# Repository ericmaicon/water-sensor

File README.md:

# About it

This is a project for a master degree with the goal of store water flow data in a house.

It uses a flow sensor, connected on an ESP8266 to send it thought the internet to an endpoint.
It has a USBSerial to update the ESP8266 firmware and code.

* [Roadmap](https://github.com/ericmaicon/water-sensor/blob/master/docs/Roadmap.md)

Some research about ESP8266:

* [Espruino firmware](https://github.com/ericmaicon/water-sensor/blob/master/docs/Espruino.md)
* [NodeLUA firmware](https://github.com/ericmaicon/water-sensor/blob/master/docs/Nodelua.md)
* [NodeMCU firmware](https://github.com/ericmaicon/water-sensor/blob/master/docs/Nodemcu.md)
* [AT firmware](https://github.com/ericmaicon/water-sensor/blob/master/docs/AT.md)

Raspberry:

* [Install Debian on Raspberry from Mac](https://github.com/ericmaicon/water-sensor/blob/master/docs/Install-Raspberry.md)
* [Using raspberry and ESP8266 as router](https://github.com/ericmaicon/water-sensor/blob/master/docs/Raspberry.md)

# Useful Links

## Schematics
* [Convert 5V to 3.3V](http://kb.kaminskiengineering.com/node/171)
* [Convert AC to DC](http://www.elprocus.com/steps-to-convert-the-230v-ac-to-5v-dc/)

## Flow Sensor
* [Sensor](http://www.seeedstudio.com/wiki/G1'1/4_Water_Flow_sensor)
* [Datasheet](http://www.seeedstudio.com/depot/datasheet/water%20flow%20sensor%20datasheet.pdf)
* [Datasheet](http://www.hobbytronics.co.uk/datasheets/sensors/YF-S201.pdf)
* [Portuguese Tutorial](http://labdegaragem.com/profiles/blogs/tutorial-como-utilizar-o-sensor-de-fluxo-de-agua)
* [Code example](http://www.hobbytronics.co.uk/download/YF-S201.ino)
* [Tutorial](http://diyhacking.com/arduino-flow-rate-sensor/)
* [Code example](http://diyhacking.com/projects/FlowMeterDIY.ino)

## ESP8266
* [GPIO API](http://esp8266.co.uk/tutorials/introduction-to-the-gpio-api/)
* [Flow Sensor and ESP8266](http://www.esp8266.com/viewtopic.php?f=18&t=5624)
* [Two ESP8266 talking](http://randomnerdtutorials.com/how-to-make-two-esp8266-talk/)
* [Log data in MySQL](https://primalcortex.wordpress.com/2015/02/19/esp8266-logging-data-in-a-mysql-database/)

## Arduino
* [Ethercard](https://github.com/jcw/ethercard)

Arduino drive on MAC:
[Drive](http://www.wch.cn/download/CH341SER_MAC_ZIP.html)
Download, install.

Run:
`sudo nvram boot-args="kext-dev-mode=1"`
reboot

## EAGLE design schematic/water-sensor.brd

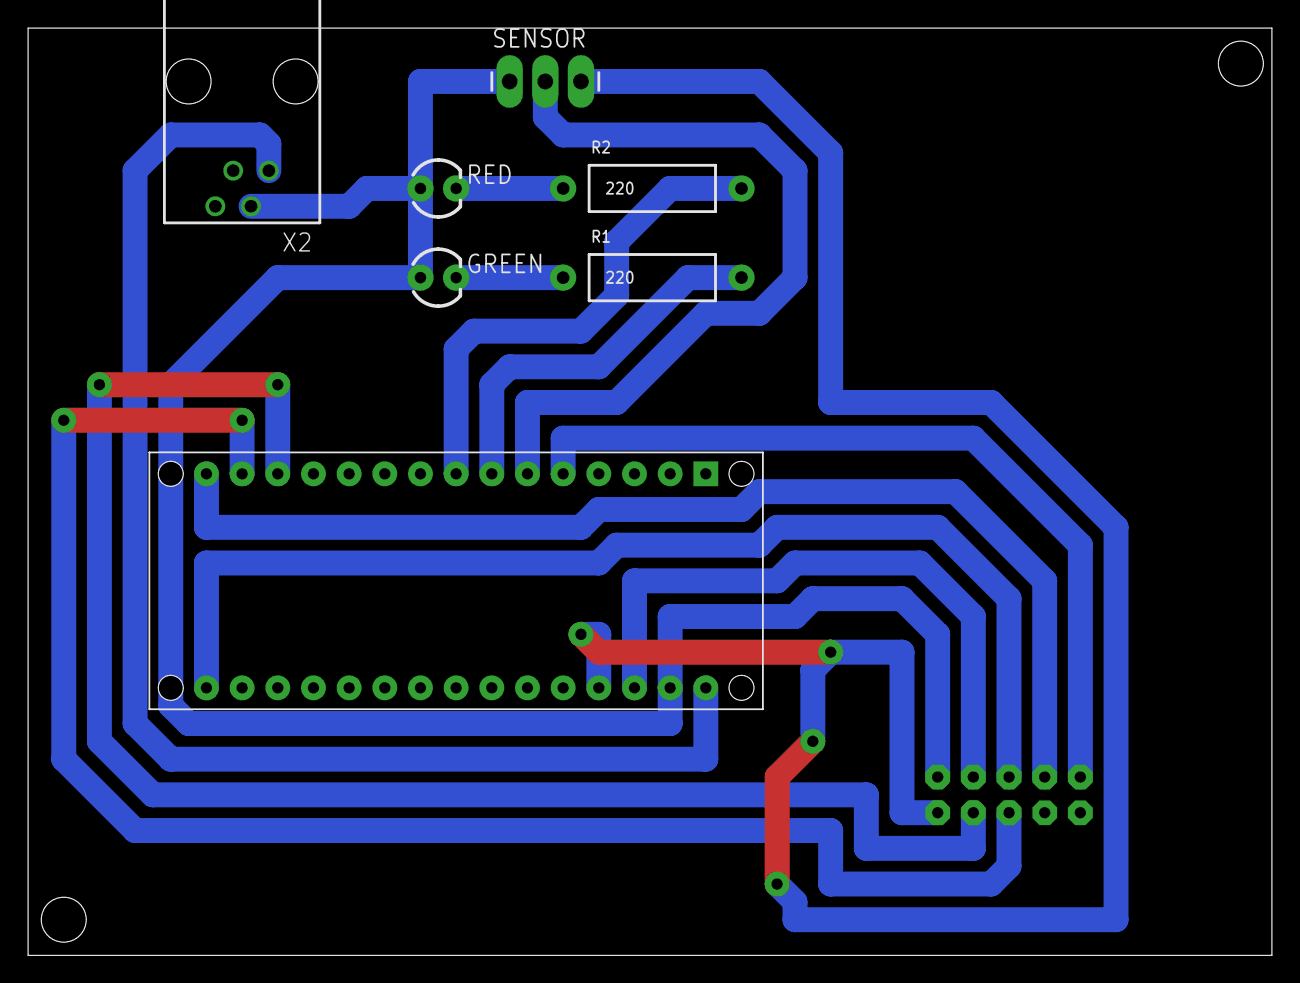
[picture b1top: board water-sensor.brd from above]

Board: 2 copper layers, 88.6 x 66.0 mm, 8 parts (1 on the bottom side), 14 nets.

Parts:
GREEN: LED3MM
R1, R2: 220; AXIAL-0.5
RED: LED3MM
SENSOR: 1X03_LONGPADS
U$1: ARDUINONANO; PDIP-32
U$2: ENC28J60ENC28J60; ENC28J60
X2: 14867

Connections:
5V: SENSOR.3, U$1.+5V, U$2.VCC
D2: U$1.D2, U$2.INT
D3: SENSOR.2, U$1.D3
D4: R1.P$2, U$1.D4
D5: R2.P$2, U$1.D5
D10: U$1.D10, U$2.CS
D11: U$1.D11, U$2.SI
D12: U$1.D12, U$2.SO
D13: U$1.D13, U$2.SCK
GND: GREEN.A, RED.A, SENSOR.1, U$1.GND1, U$2.GND, X2.2
unnamed: GREEN.K, R1.P$1
unnamed: R2.P$1, RED.K
RESET: U$1.RESET1, U$2.RESET
VIN: U$1.VIN, X2.1

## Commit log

2015-11-22 init repository
2015-11-22 Docs
2015-11-22 doc refactor
2015-11-22 fixing roadmap name
2015-11-22 doing the first hello world with the sensor. Create the structure on raspberry to received infos from others esp8266
2015-11-22 raspberry hello world
2015-11-25 receive and sync method
2015-11-28 js part to receive records and sync with mysql DO done
2015-11-30 raspberry doc and prepare js script
2015-11-30 small fix on main.js
2015-12-01 change sync and receive to log everything
2015-12-01 receive.conf
2015-12-01 receive.sh fix
2015-12-01 test receive.service to avoid crash on services
2015-12-01 crontab docs
2015-12-01 change raspberry esp code
2015-12-02 fixing the init.lua and the raspberry one
2015-12-02 changing from express to serial reader
2015-12-02 fixing the receiver serial
2015-12-10 update the PCB
2015-12-12 fixing some docs mistakes
2015-12-12 updating docs
2015-12-12 avoid commit log
2016-01-31 change the project scope to use arduino together with ESP8266
2016-02-13 espiobridge tutorial
2016-02-13 nodemcu change
2016-02-14 arduino code
2016-02-21 enc28j60 schematic
2016-02-28 new schematic with enc28j60
2016-03-12 arduino schema update
2016-03-12 power schema
2016-03-12 small change on arudino.ino
2016-03-14 final code from arduino running the water sensor
2016-03-21 sensor schematic
2016-03-21 water sensor
2016-07-14 change on the restart logic
2016-09-01 changes in the main code
2016-09-26 change to mqtt
2016-11-04 little changes on arduino.ino
2017-02-01 arduino changes

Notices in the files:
parts and their libraries:
SparkFun-Connectors: Licensing: Creative Commons ShareAlike 4.0 International - https://creativecommons.org/licenses/by-sa/4.0
